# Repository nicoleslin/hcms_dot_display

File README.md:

# hcms_dot_display
repo for board files and drivers for hp hcms dot displays

## link dump
https://github.com/SpenceKonde/megaTinyCore/blob/master/megaavr/extras/ATtiny_x26.md
https://teddywarner.org/Projects/SerialUPDI/
https://github.com/SpenceKonde/AVR-Guidance/blob/master/UPDI/jtag2updi.md
http://ad7i.net/main/analysis-of-resistor-values-for-pymcuprog-usbusart-serial-programming/
https://www.mouser.com/ProductDetail/Apem/MHPS2283?qs=%2Fs1LKTamv0woxsbKv1Ncmw%3D%3D

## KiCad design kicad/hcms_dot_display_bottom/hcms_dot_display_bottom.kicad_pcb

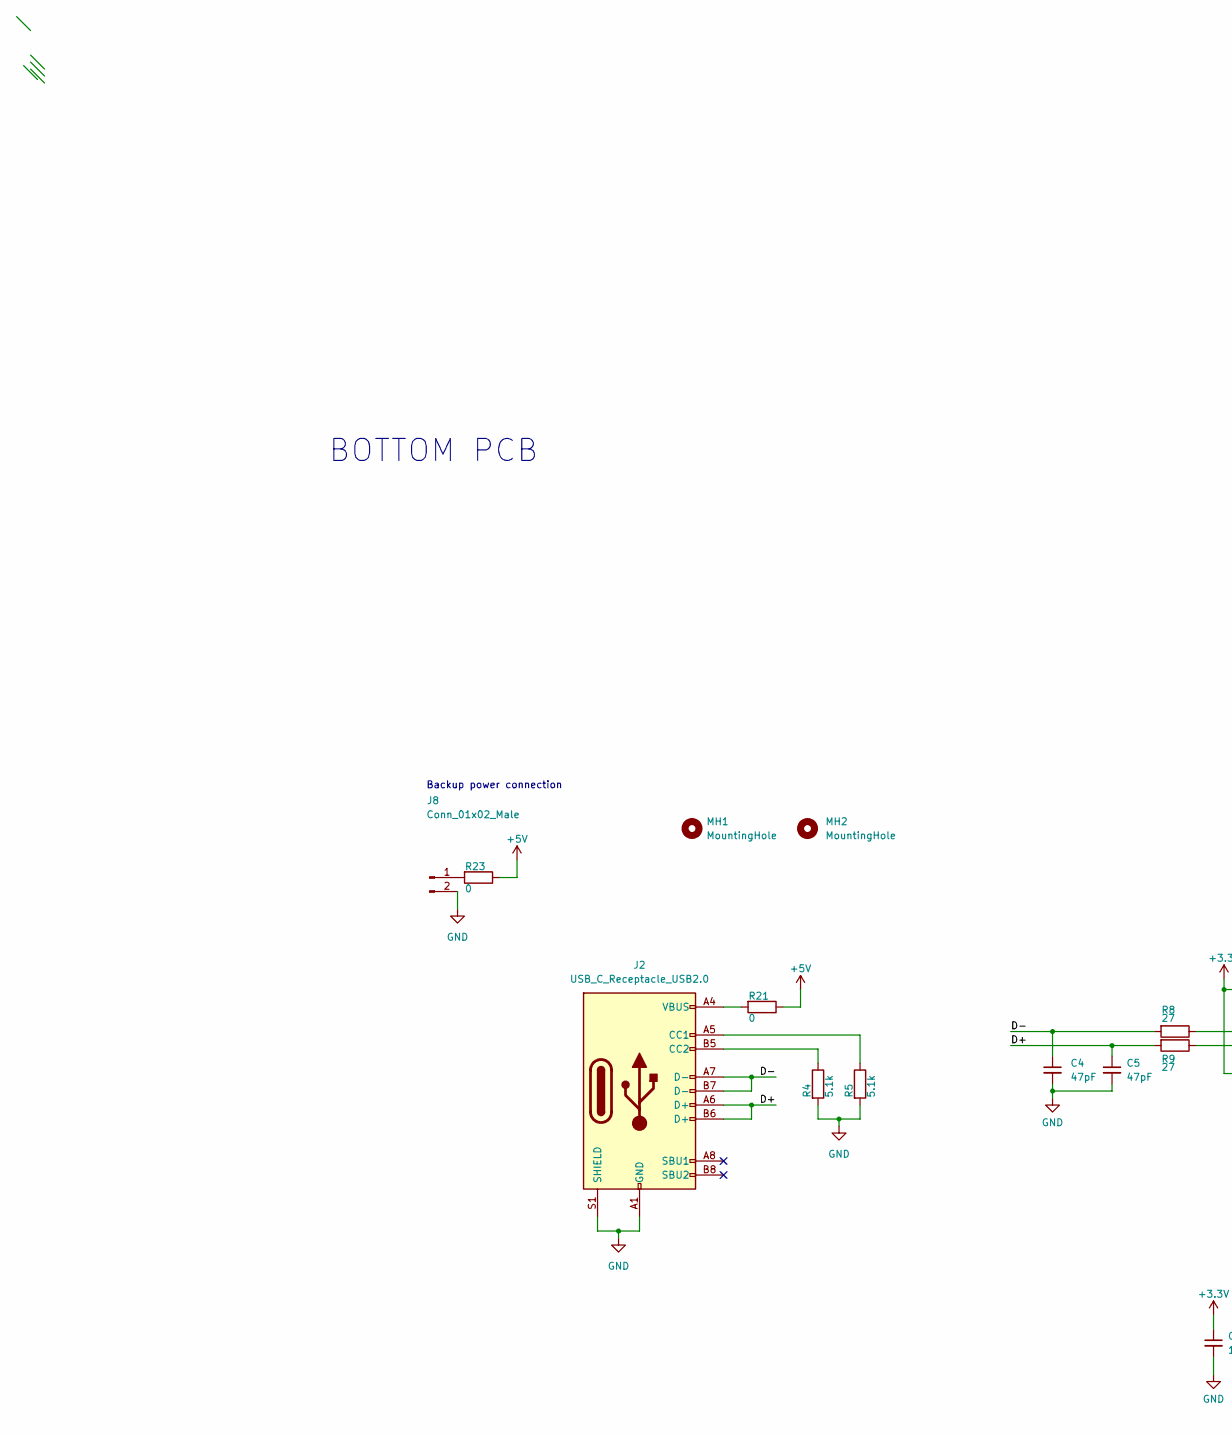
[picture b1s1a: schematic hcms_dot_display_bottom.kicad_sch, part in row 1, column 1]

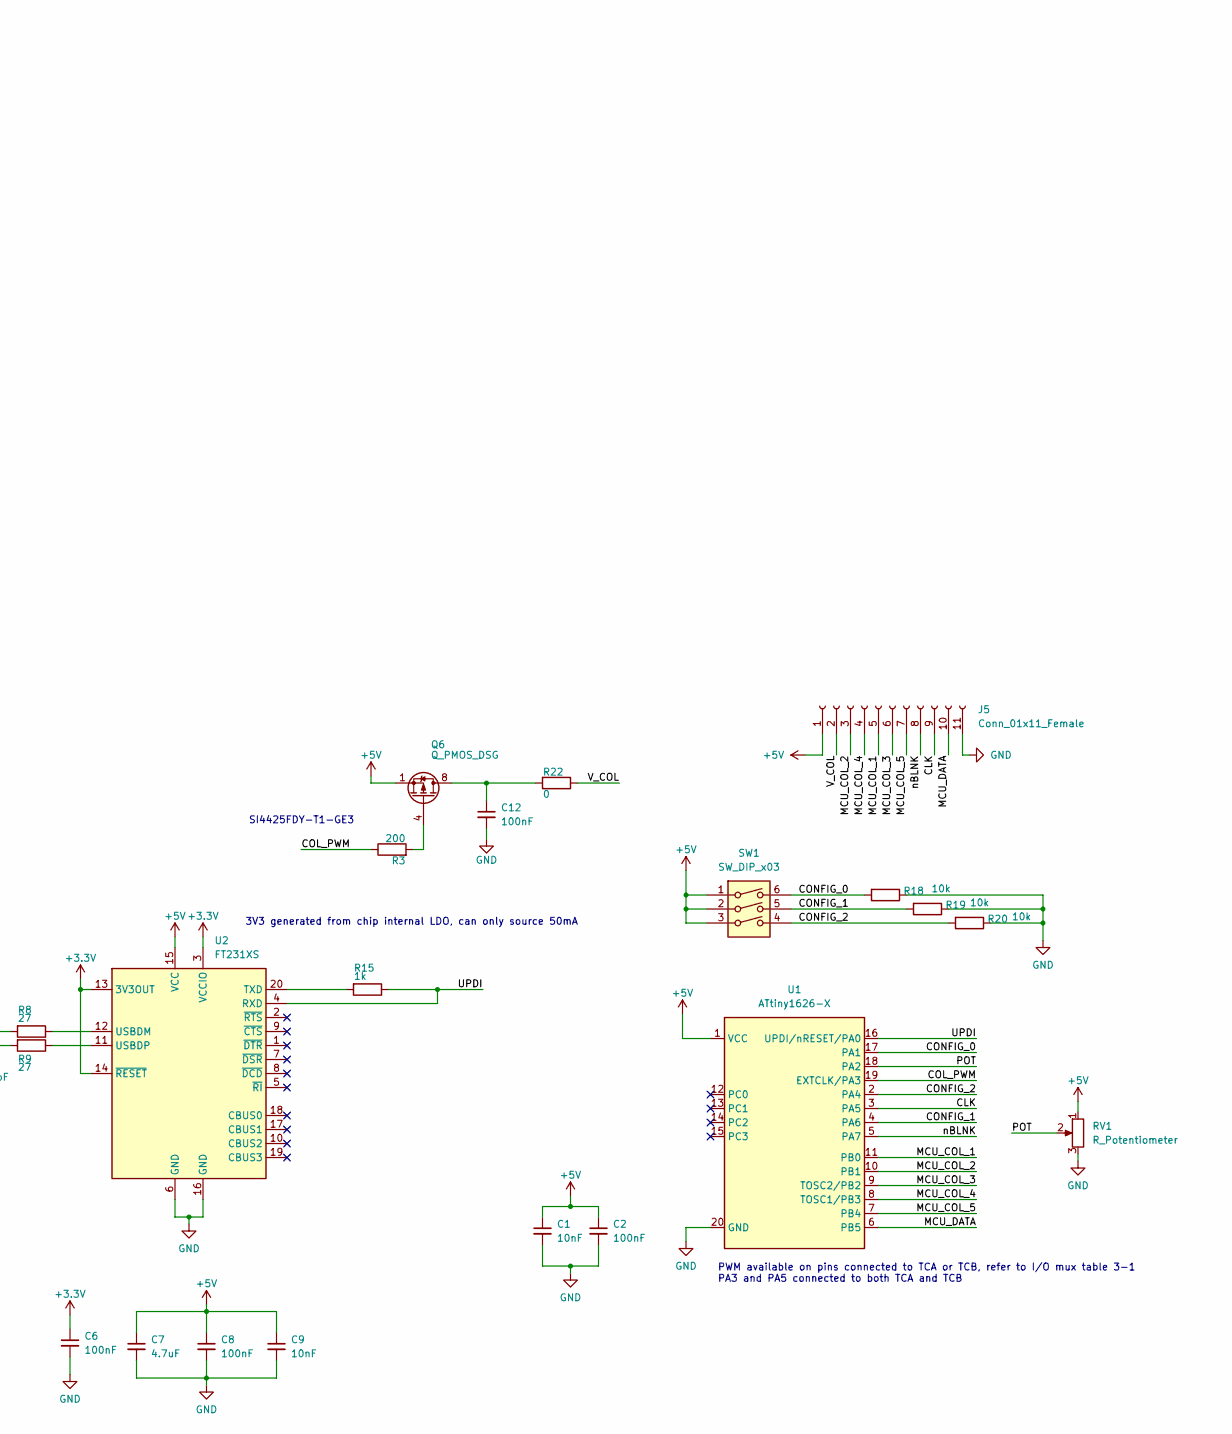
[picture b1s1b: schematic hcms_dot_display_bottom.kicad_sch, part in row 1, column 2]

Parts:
C1, C9: 10nF; C_0603_1608Metric
C2, C6, C8, C12: 100nF; C_0603_1608Metric
C4, C5: 47pF; C_0603_1608Metric
C7: 4.7uF; C_0603_1608Metric
J2: USB_C_Receptacle_USB2.0; 213716-0001
J5: Conn_01x11_Female; PinSocket_1x11_P2.54mm_Vertical
J8: Conn_01x02_Male; PinHeader_1x02_P2.54mm_Vertical
MH1, MH2: MountingHole; MountingHole_2.2mm_M2_Pad_Via
Q6: Q_PMOS_DSG; SO-8_5.3x6.2mm_P1.27mm
R3: 200; R_0603_1608Metric
R4, R5: 5.1k; R_0603_1608Metric
R8, R9: 27; R_0603_1608Metric
R15: 1k; R_0603_1608Metric
R18, R19, R20: 10k; R_0603_1608Metric
R21, R22, R23: 0; R_0603_1608Metric
RV1: R_Potentiometer; TRIM_3352T-1-201LF
SW1: SW_DIP_x03; BPA03SB
U1: ATtiny1626-X; SSOP-20_5.3x7.2mm_P0.65mm
U2: FT231XS; SSOP-20_3.9x8.7mm_P0.635mm

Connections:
+3V3: C6.1, U2.3 (VCCIO), U2.13 (3V3OUT), U2.14 (~RESET)
+5V: C1.1, C2.1, C7.1, C8.1, C9.1, J5.1, Q6.1 (S), Q6.2 (S), Q6.3 (S), R21.1, R23.1, RV1.1, SW1.1, SW1.2, SW1.3, U1.1 (VCC), U2.15 (VCC)
/CLK: J5.9, U1.3 (PA5)
/COL_PWM: R3.1, U1.19 (EXTCLK/PA3)
/CONFIG_0: R18.2, SW1.6, U1.17 (PA1)
/CONFIG_1: R19.2, SW1.5, U1.4 (PA6)
/CONFIG_2: R20.2, SW1.4, U1.2 (PA4)
/D+: C5.1, J2.A6 (D+), J2.B6 (D+), R9.2
/D-: C4.1, J2.A7 (D-), J2.B7 (D-), R8.2
/MCU_COL_1: J5.5, U1.11 (PB0)
/MCU_COL_2: J5.3, U1.10 (PB1)
/MCU_COL_3: J5.6, U1.9 (TOSC2/PB2)
/MCU_COL_4: J5.4, U1.8 (TOSC1/PB3)
/MCU_COL_5: J5.7, U1.7 (PB4)
/MCU_DATA: J5.10, U1.6 (PB5)
/POT: RV1.2, U1.18 (PA2)
/UPDI: R15.1, U1.16 (UPDI/nRESET/PA0), U2.4 (RXD)
/V_COL: J5.2, R22.1
/nBLNK: J5.8, U1.5 (PA7)
GND: C1.2, C2.2, C4.2, C5.2, C6.2, C7.2, C8.2, C9.2, C12.2, J2.A1 (GND), J2.A12 (GND), J2.B1 (GND), J2.B12 (GND), J2.S1 (SHIELD), J5.11, J8.2, R4.2, R5.2, R18.1, R19.1, R20.1, RV1.3, U1.20 (GND), U2.6 (GND), U2.16 (GND)
unnamed: C12.1, Q6.5 (D), Q6.6 (D), Q6.7 (D), Q6.8 (D), R22.2
unnamed: J2.A4 (VBUS), J2.A9 (VBUS), J2.B4 (VBUS), J2.B9 (VBUS), R21.2
unnamed: J2.A5 (CC1), R5.1
unnamed: J2.B5 (CC2), R4.1
unnamed: J8.1, R23.2
unnamed: Q6.4 (G), R3.2
unnamed: R8.1, U2.12 (USBDM)
unnamed: R9.1, U2.11 (USBDP)
unnamed: R15.2, U2.20 (TXD)

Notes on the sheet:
BOTTOM PCB
3V3 generated from chip internal LDO, can only source 50mA
PWM available on pins connected to TCA or TCB, refer to I/O mux table 3-1 PA3 and PA5 connected to both TCA and TCB
SI4425FDY-T1-GE3
Backup power connection

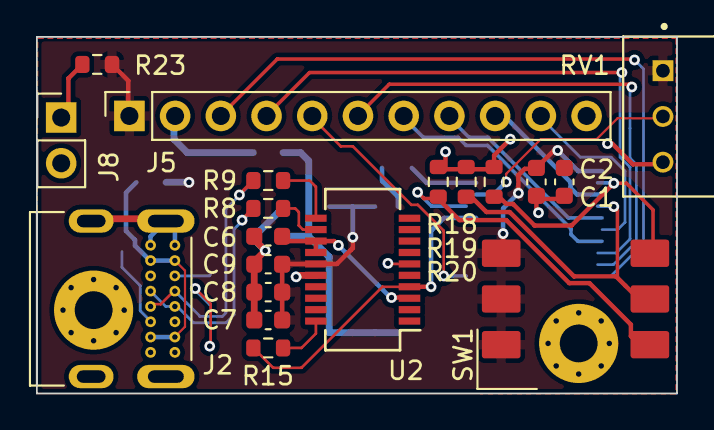
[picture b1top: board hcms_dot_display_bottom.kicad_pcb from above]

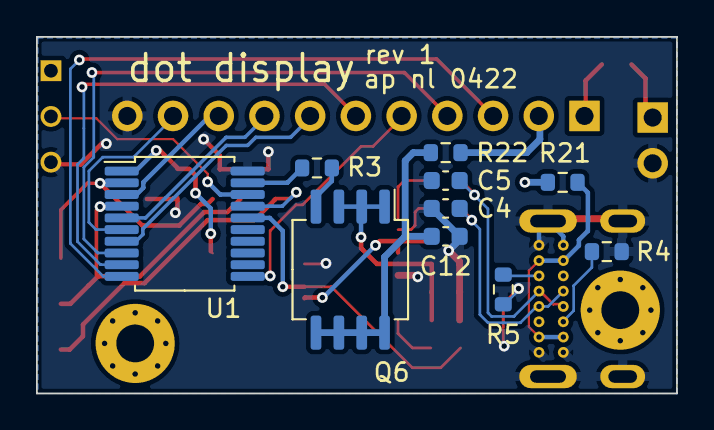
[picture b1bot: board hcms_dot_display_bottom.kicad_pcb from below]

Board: 2 copper layers, 35.6 x 19.8 mm, 31 parts (12 on the bottom side), 29 nets.

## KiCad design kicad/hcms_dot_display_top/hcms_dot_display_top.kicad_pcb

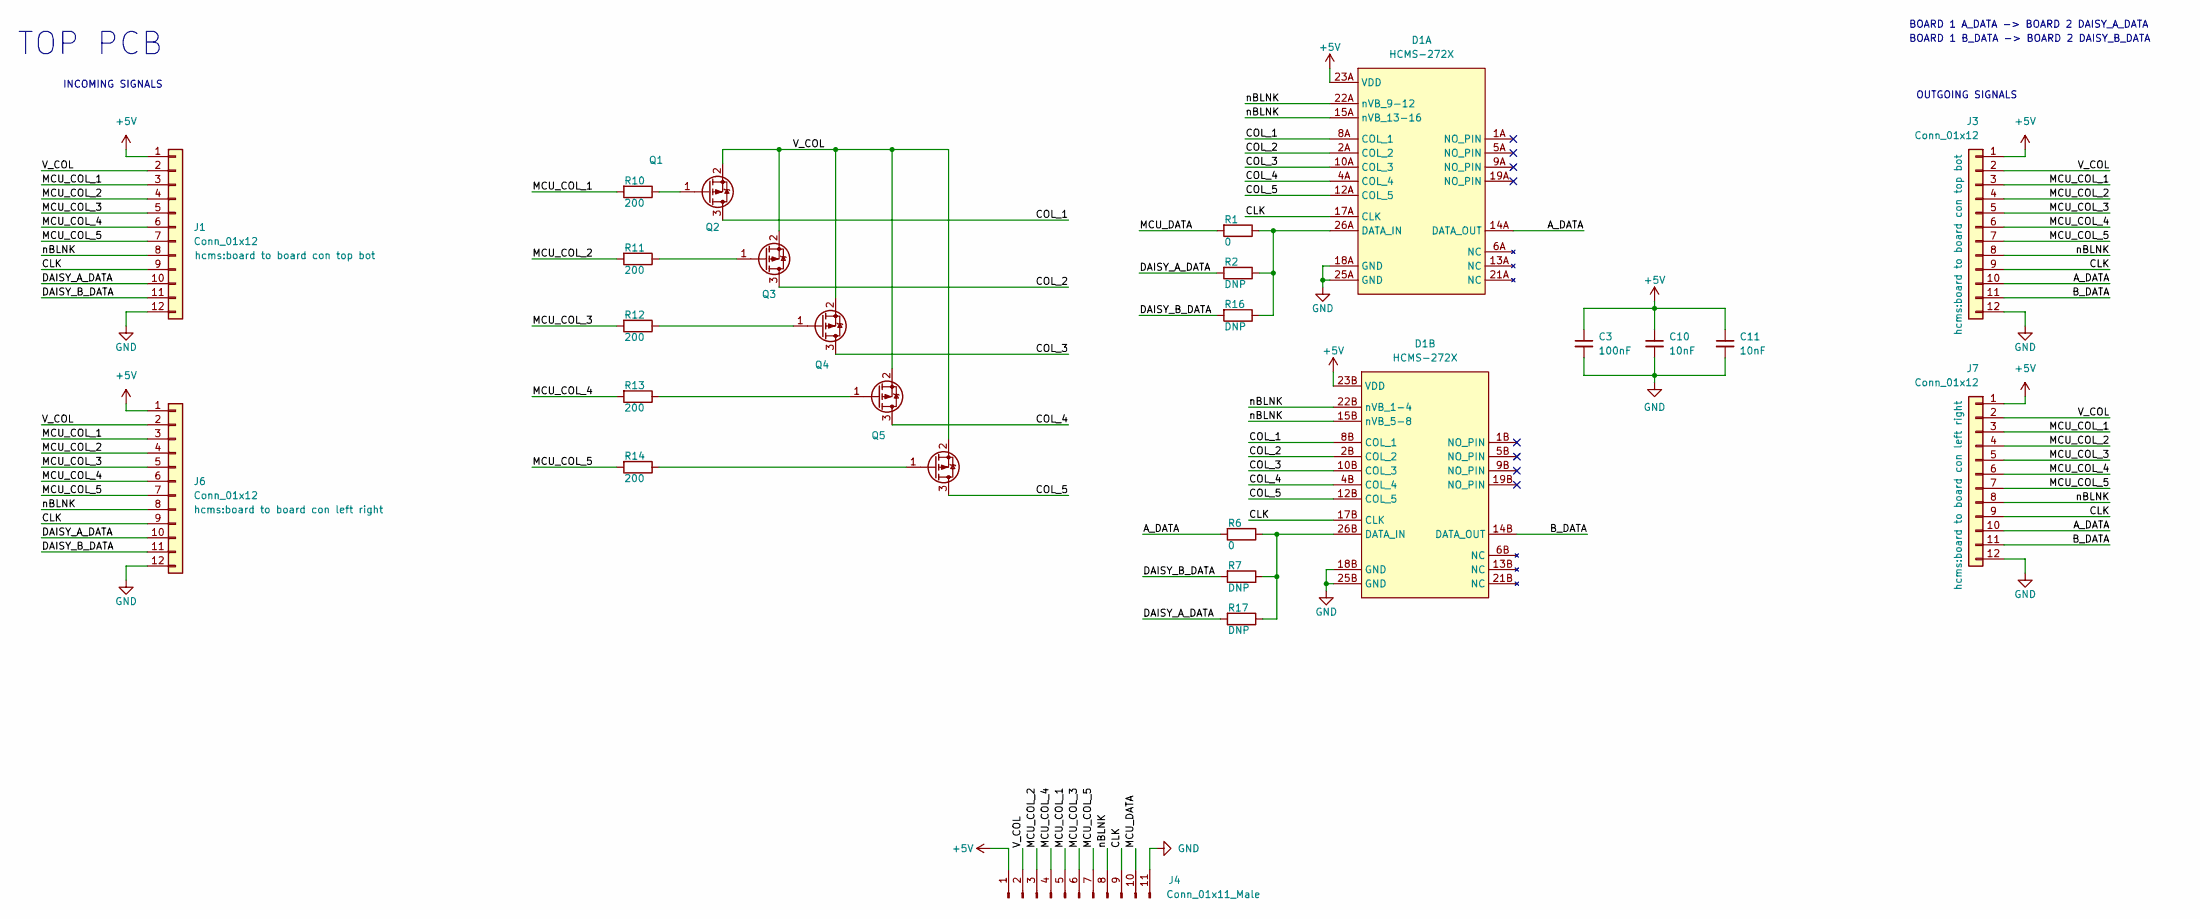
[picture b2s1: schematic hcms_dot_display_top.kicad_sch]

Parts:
C3: 100nF; C_0603_1608Metric
C10, C11: 10nF; C_0603_1608Metric
D1: HCMS-272X; HCMS-2722
J1, J3: Conn_01x12; board to board con top bot
J4: Conn_01x11_Male; PinHeader_1x11_P2.54mm_Vertical
J6, J7: Conn_01x12; board to board con left right
Q1, Q2, Q3, Q4, Q5: (no value)
R1, R6: 0; R_0603_1608Metric
R2, R7, R16, R17: DNP; R_0603_1608Metric
R10, R11, R12, R13, R14: 200; R_0603_1608Metric

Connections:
+5V: C3.1, C10.1, C11.1, D1.23A (VDD), D1.23B (VDD), J1.1, J3.1, J4.1, J6.1, J7.1
/A_DATA: D1.14A (DATA_OUT), J3.10, J7.10, R6.2
/B_DATA: D1.14B (DATA_OUT), J3.11, J7.11
/CLK: D1.17A (CLK), D1.17B (CLK), J1.9, J3.9, J4.9, J6.9, J7.9
/COL_1: D1.8A (COL_1), D1.8B (COL_1), Q1.3 (D)
/COL_2: D1.2A (COL_2), D1.2B (COL_2), Q2.3 (D)
/COL_3: D1.10A (COL_3), D1.10B (COL_3), Q3.3 (D)
/COL_4: D1.4A (COL_4), D1.4B (COL_4), Q4.3 (D)
/COL_5: D1.12A (COL_5), D1.12B (COL_5), Q5.3 (D)
/DAISY_A_DATA: J1.10, J6.10, R2.2, R17.2
/DAISY_B_DATA: J1.11, J6.11, R7.2, R16.2
/MCU_COL_1: J1.3, J3.3, J4.5, J6.3, J7.3, R10.2
/MCU_COL_2: J1.4, J3.4, J4.3, J6.4, J7.4, R11.2
/MCU_COL_3: J1.5, J3.5, J4.6, J6.5, J7.5, R12.2
/MCU_COL_4: J1.6, J3.6, J4.4, J6.6, J7.6, R13.2
/MCU_COL_5: J1.7, J3.7, J4.7, J6.7, J7.7, R14.2
/MCU_DATA: J4.10, R1.2
/V_COL: J1.2, J3.2, J4.2, J6.2, J7.2, Q1.2 (S), Q2.2 (S), Q3.2 (S), Q4.2 (S), Q5.2 (S)
/nBLNK: D1.15A (nVB_13-16), D1.15B (nVB_5-8), D1.22A (nVB_9-12), D1.22B (nVB_1-4), J1.8, J3.8, J4.8, J6.8, J7.8
GND: C3.2, C10.2, C11.2, D1.18A (GND), D1.18B (GND), D1.25A (GND), D1.25B (GND), J1.12, J3.12, J4.11, J6.12, J7.12
unnamed: D1.26A (DATA_IN), R1.1, R2.1, R16.1
unnamed: D1.26B (DATA_IN), R6.1, R7.1, R17.1
unnamed: Q1.1 (G), R10.1
unnamed: Q2.1 (G), R11.1
unnamed: Q3.1 (G), R12.1
unnamed: Q4.1 (G), R13.1
unnamed: Q5.1 (G), R14.1

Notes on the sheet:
BOARD 1 A_DATA -> BOARD 2 DAISY_A_DATA
BOARD 1 B_DATA -> BOARD 2 DAISY_B_DATA
INCOMING SIGNALS
OUTGOING SIGNALS
TOP PCB

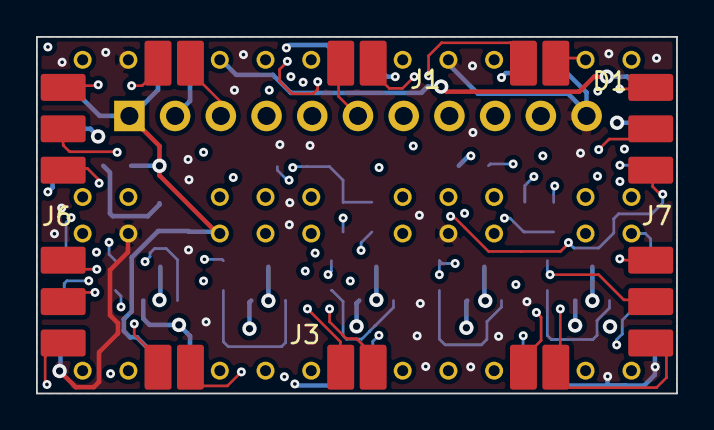
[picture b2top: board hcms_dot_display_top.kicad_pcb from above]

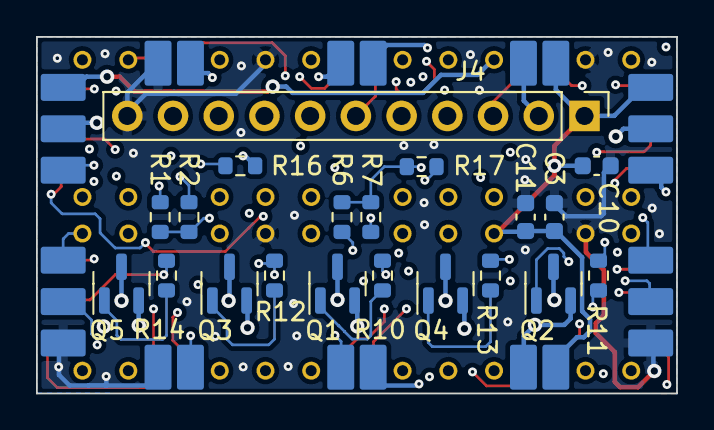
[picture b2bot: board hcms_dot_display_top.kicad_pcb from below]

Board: 4 copper layers, 35.6 x 19.8 mm, 25 parts (20 on the bottom side), 27 nets.

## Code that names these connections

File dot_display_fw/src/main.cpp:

#include <Arduino.h>
#define SW_CONFIG_0_PIN 14 // PA1
#define SW_CONFIG_1_PIN 2  // PA6
#define SW_CONFIG_2_PIN 0  // PA4
#define POT_PIN         15 // PA2
#define CLK_PIN         1  // PA5
#define COL_PWM_PIN     16 // PA3
#define nBLNK_PIN       3  // PA7
#define MCU_COL_1_PIN   9  // PB0
#define MCU_COL_2_PIN   8  // PB1
#define MCU_COL_3_PIN   7  // PB2
#define MCU_COL_4_PIN   6  // PB3
#define MCU_COL_5_PIN   5  // PB4
#define MCU_DATA_PIN    4  // PB5

void setup() {
  // put your setup code here, to run once:
  // Serial.begin(9600);
  pinMode(SW_CONFIG_0_PIN, INPUT);
  pinMode(SW_CONFIG_1_PIN, INPUT);
  pinMode(SW_CONFIG_2_PIN, INPUT);
  pinMode(POT_PIN, INPUT);
  pinMode(CLK_PIN, OUTPUT);
  pinMode(COL_PWM_PIN, OUTPUT);
  pinMode(nBLNK_PIN, OUTPUT);
  pinMode(MCU_COL_1_PIN, OUTPUT);
  pinMode(MCU_COL_2_PIN, OUTPUT);
  pinMode(MCU_COL_3_PIN, OUTPUT);
  pinMode(MCU_COL_4_PIN, OUTPUT);
  pinMode(MCU_COL_5_PIN, OUTPUT);
  pinMode(MCU_DATA_PIN, OUTPUT);
}

void loop() {
  // put your main code here, to run repeatedly:
  // Serial.println("hi");
  // delay(1000);
}

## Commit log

2022-03-27 initial kicad commit
2022-03-30 progress from 0329
2022-03-31 battery dying
2022-03-31 aidan
2022-04-01 Reduce number of FETs, cleaned up schematic added some footprints, and starting routing
2022-04-02 Added PNs for push button and pot with basic footprints, updated some resistor values
2022-04-02 layout
2022-04-02 slight mods to UPDI circuits
2022-04-02 Updated dot matrix footprint, experimented with stacked control board design
2022-04-02 Cleaned up layout strat
2022-04-03 fixed pot footprint, updated layout from schematics, changed board to board conn sch sym from 13 pin to 11 pin, reorgd sch sym to reflect stacked board design, added decoupling caps to top board
2022-04-04 fixed some footprints and edited placement
2022-04-05 3d model environment variables lol
2022-04-07 progress from 0406
2022-04-08 updated micro to have more i/o
2022-04-09 pughe
2022-04-09 Added Vcol rail and switching PMOS. Started new board to board cons
2022-04-09 literally in the middle of fixing left right conn but time to climb
2022-04-10 beginning of ecos
2022-04-10 aidan im pushing
2022-04-10 added switch fp, cleaned up placement. ready for routing
2022-04-10 will fix?
2022-04-10 finally gonna start routing ??
2022-04-10 Updated DRC rules to match JLCPCB guide
2022-04-10 I did a lot of routing lol
2022-04-10 moar route
2022-04-10 Finished first draft of display board routing
2022-04-10 Finished first draft of MCU board routing
2022-04-10 Fixed min angular ring DRC, increased via size t0 .2mm .5mm
2022-04-11 Fixed USB footprint to accomodate DRCs
2022-04-11 ready for layout review
2022-04-16 layout ready for review i think
2022-04-16 aidan take the wheel
2022-04-16 splitting boards into 2 projects
2022-04-16 Top board refined
2022-04-16 progress making bottom manufacturable
2022-04-26 Updated DRCs and fixed connector edge clearance
2022-04-26 fuck ya
2022-04-26 easter eggs, actually ready for final review. boards passing DRC
2022-04-26 checked DRC one more time
2022-05-01 edits to top
2022-05-02 Updated DMP footprint on bottom board and re routed
2022-05-02 changes to bottom
2022-05-03 ran DRC on top
2022-05-03 Fixed daisy issue left right
2022-05-03 gerbers
2022-05-03 bottom gerbers
2022-05-14 pushing fw
2022-05-14 first fw push
2022-05-15 added pins to cpp file
2022-05-15 Excel sheet with MCU timing and power estimates
2022-05-15 computer reboot
2022-05-15 desperation
2022-05-15 code for display
2022-05-15 clock transition update
2022-05-15 col 5 not working for some reason
2022-06-12 arduino files
2022-06-12 random init pattern
